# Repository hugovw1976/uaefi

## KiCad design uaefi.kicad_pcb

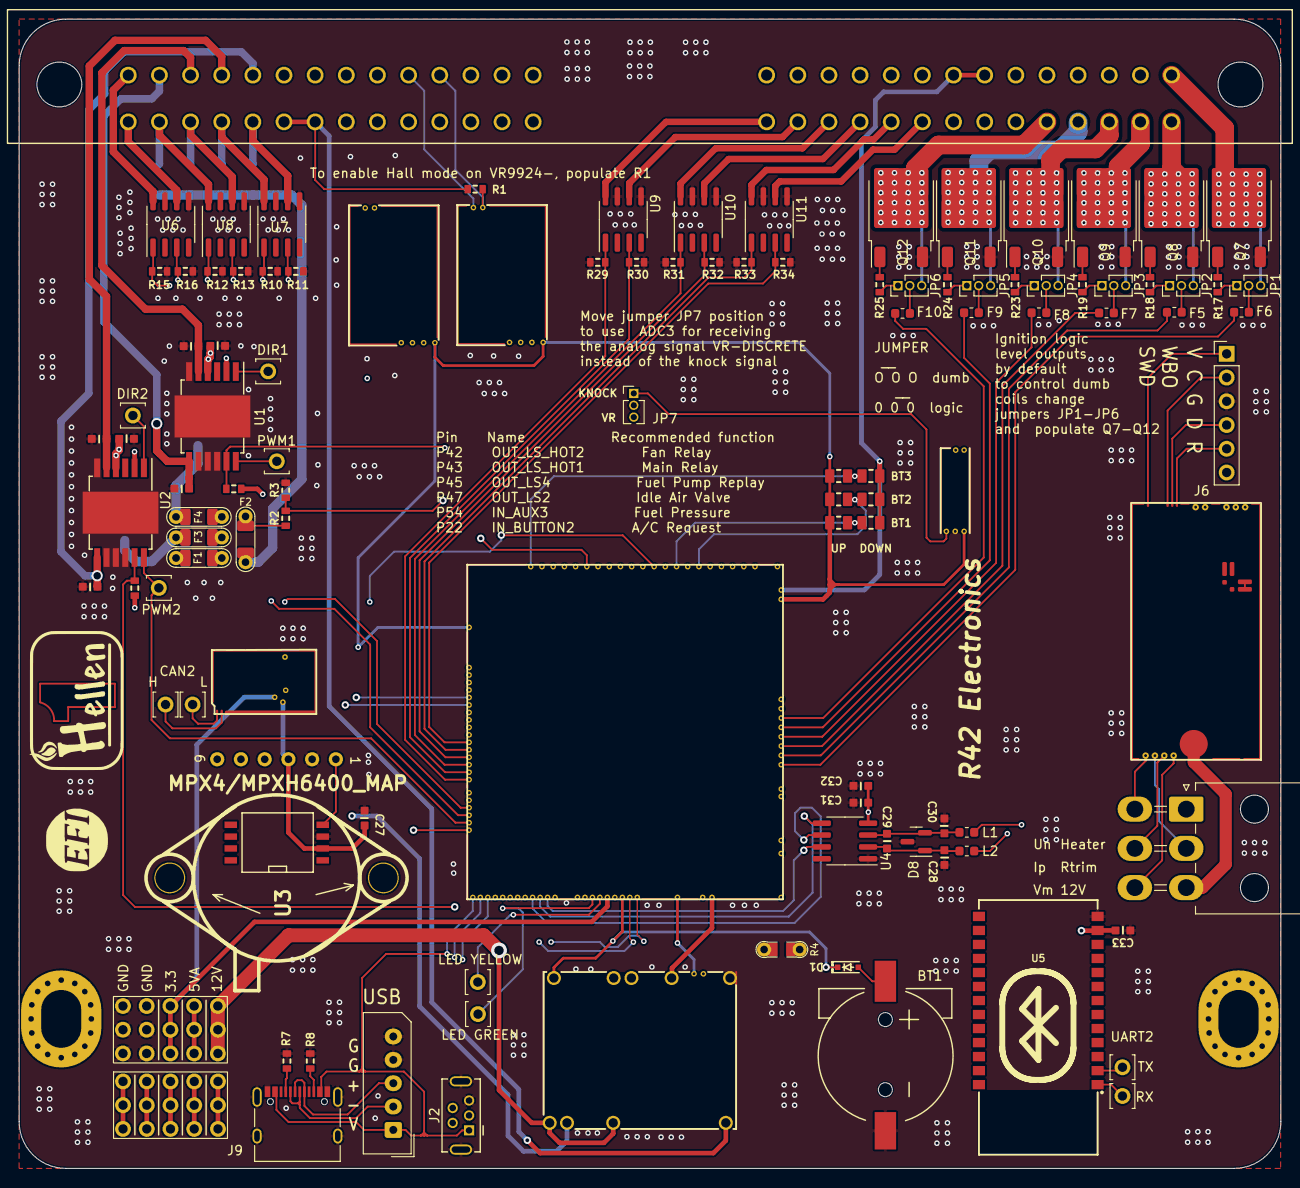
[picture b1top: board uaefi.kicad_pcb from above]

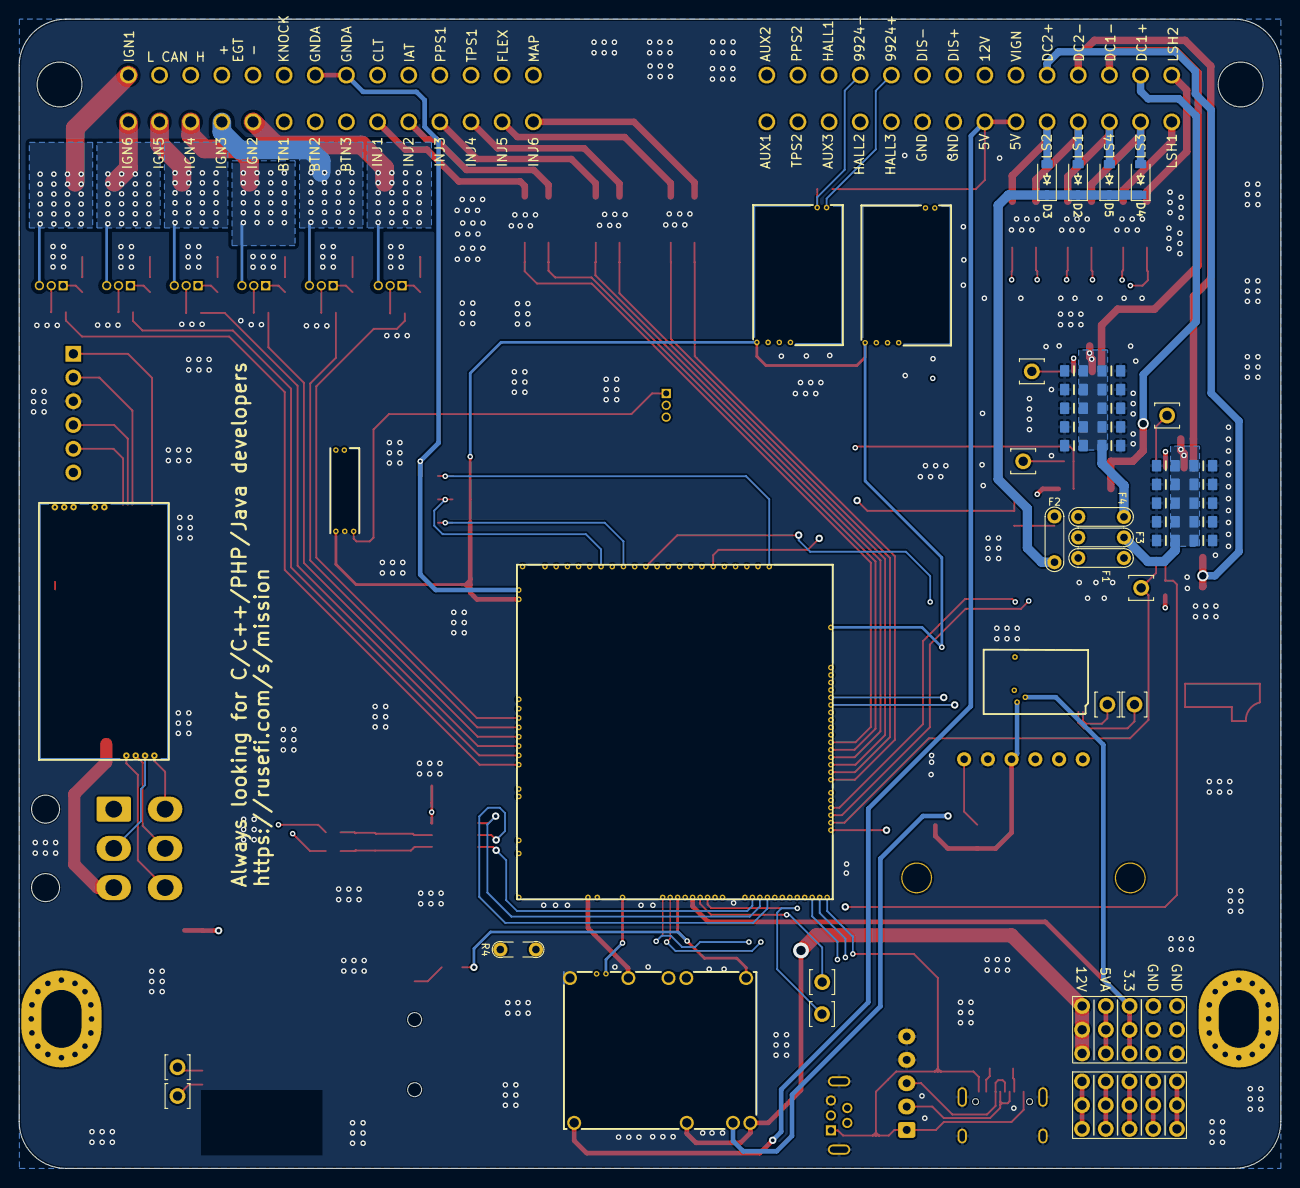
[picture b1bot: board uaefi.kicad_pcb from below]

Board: 4 copper layers, 135.0 x 123.0 mm, 137 parts (24 on the bottom side), 151 nets.

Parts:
BT1: CR1220; CR1220-2
C1, C2, C3, C4, C5, C6, C7, C8, C9, C10, C14, C15, C16, C17, C18, C19, C20, C21, C22, C23: 10u; C0805
C11, C24, C27, C29, C31, C33: 100n; C0603
C12, C13, C25, C26, C28, C30: 10n; C0603
C32: 1u; C0603
D1: 1N4148WS; SOD-323
D2, D3, D4, D5: B5819W; SOD-123
D8: NUP2105L; SOT-23
F1, F2, F3, F4: 12H1500D; PAD-1206-PAD
F5, F6, F7, F8, F9, F10: 50mA; Fuse_0603_1608Metric
G1: RUSEFI_LOGO; rusefi_logo
G2: LOGO
G3, G4: PROTO_AREA
H1: M4; MountingHole_4.3x6.2mm_M4_Pad_Via
H2: M3; MountingHole_4.3x6.2mm_M4_Pad_Via
J1: 211PL562L0011; 211PL562L0011_2
J2: USB_B_Mini; USB-MINI-B-VERTICAL
J3: 5569-06A2; Molex_Mini-Fit_Jr_5569-06A2_2x03_P4.20mm_Horizontal
J6: Conn_01x06; PinHeader_1x06_P2.54mm_Vertical
J7: Conn_01x05_Male; Molex_SPOX_5267-05A_1x05_P2.50mm_Vertical
J9: USB_C
JP1, JP2, JP3, JP4, JP5, JP6, JP7: Jumper_3_Open; PinHeader_1x03_P1.27mm_Vertical
L1, L2: 470R@100MHz; L_0603_1608Metric
M1: Module-power_12and5V-0.2; power_12and5V
M2: Module-knock-0.2; knock
M3: Module-vr-discrete-0.5; vr-discrete
M4: Module-vr-max9924-0.1; vr-max9924
M5: Module-wbo-0.5; wbo
M6: Module:mega-mcu100/0.3; mega-mcu100
M7: Module-can-0.1; can
P1, P2, P3, P4, P7, P8, P15, P16, P17, P18: Pad; PAD-TH
Q7, Q8, Q9, Q10, Q11, Q12: ISL9V3040D3ST; TO-252-2
R1, R9, R10, R11, R12, R13, R14, R15, R16, R29, R30, R31, R32, R33, R34: 4.7k; R0603
R2: 33k; R0603
R3: 6.8k; R0603
R4: Jumper-Pad-Pad; PAD-0805-PAD
R7, R8: 5.6k; R0603
R17, R18, R19, R23, R24, R25: 22; R0603
R35, R36, R37: 10k; R0805
R38, R39, R40: DNP; R0805
U1, U2: TLE9201SG; Infineon_PG-DSO-12-11
U3: MPX4/MPXH6400_MAP; MPX-4_MAP
U4: MAX31855KASA; SOIC-8_3.9x4.9mm_P1.27mm
U5: JDY-33
U6, U7, U8, U9, U10, U11: VNLD5160TR-E; SOIC-8_3.9x4.9mm_P1.27mm

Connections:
+3.3V: M6.N21 (V33), R9.2, R14.2, U1.2 (VSO), U2.2 (VSO)
+3.3VA: C31.2, C32.2, C33.2, G3.3, G3.8, G3.13, M6.N15 (V33_SWITCHABLE), M7.V2 (CAN_VIO), U4.4 (V_CC), U5.12 (3V3)
+5V: M1.E4 (V5), M6.N22 (VCC)
+5VA: C27.2, G3.4, G3.9, G3.14, M2.E1 (V5A), M3.E4 (V5_IN), M4.E4 (V5_IN), M5.W1 (V5_IN), M6.E1 (V5A_SWITCHABLE), M6.W2 (V5A_SWITCHABLE), M7.V1 (V5), R38.2, R39.2, R40.2, U3.3 (VCC)
+5VP: J1.P48 (48), J1.P49 (49), M1.V4 (5VP), R1.1
+12V: F2.1, F3.1, F4.1, J1.P37 (37), R2.2
+12V_RAW: D2.1 (K), D3.1 (K), D4.1 (K), D5.1 (K), F2.2, G3.5, G3.10, G3.15, J3.1, M1.V1 (V12_PERM), M1.V3 (V12_RAW)
/12V_KEY: F1.1, J1.P36 (36)
/ADC3: JP7.2 (C), M6.S15 (IN_KNOCK_(PA2))
/CAN+: J1.P3 (3), M5.W4 (CANH), M6.W11 (CANH)
/CAN-: J1.P2 (2), M5.W3 (CANL), M6.W12 (CANL)
/DC1_DIR: M6.E21 (OUT_PWM4_(PC8)), P15.1, U1.1 (DIR)
/DC1_DIS: M6.E8 (SPI2_MISO_(PB14)), R9.1, U1.11 (DIS)
/DC1_PWM: M6.E20 (OUT_PWM3_(PC7)), P17.1, U1.12 (PWM)
/DC2_DIR: M6.E9 (SPI2_MOSI_(PB15)), P16.1, U2.1 (DIR)
/DC2_DIS: M6.N4 (USBID_(PA10)), R14.1, U2.11 (DIS)
/DC2_PWM: M6.E22 (OUT_PWM5_(PC9)), P18.1, U2.12 (PWM)
/DC Driver 1/PWR: C1.2, C2.2, C3.2, C4.2, C5.2, C6.2, C7.2, C8.2, C9.2, C10.2, C11.2, F4.2, U1.4 (VS)
/DC Driver 2/PWR: C14.2, C15.2, C16.2, C17.2, C18.2, C19.2, C20.2, C21.2, C22.2, C23.2, C24.2, F3.2, U2.4 (VS)
/EGT+: J1.P4 (4), L1.1
/EGT-: J1.P5 (5), L2.1
/EGT/SPI_CS: M6.N9 (SPI3_CS_(PA15)), U4.6 (~CS)
/EGT/SPI_SCK: M6.N10 (SPI3_SCK_(PC10)), U4.5 (SCK)
/EGT/SPI_SO: M6.N11 (SPI3_MISO_(PC11)), U4.7 (SO)
/IGN1: F6.2, M6.W10 (IGN1_(PC13))
/IGN2: F5.2, M6.W9 (IGN2_(PE5))
/IGN3: F7.2, M6.W8 (IGN3_(PE4))
/IGN4: F8.2, M6.W7 (IGN4_(PE3))
/IGN5: F9.2, M6.W6 (IGN5_(PE2))
/IGN6: F10.2, M6.W5 (IGN6_(PB8))
/INJ1: M6.E17 (OUT_INJ1_(PD3)), R29.2, U9.1 (IN1)
/INJ2: M6.E16 (OUT_INJ2_(PA9)), R30.2, U9.3 (IN2)
/INJ3: M6.E15 (OUT_INJ3_(PD11)), R31.2, U10.1 (IN1)
/INJ4: M6.E14 (OUT_INJ4_(PD10)), R32.2, U10.3 (IN2)
/INJ5: M6.E13 (OUT_INJ5_(PD2)), R33.2, U11.1 (IN1)
/INJ6: M6.E12 (OUT_INJ6_(PA8)), R34.2, U11.3 (IN2)
/INTERNAL_MAP: M6.S12 (IN_MAP2_(PC1)), U3.1 (VOUT)
/IN_AUX1: J1.P56 (56), M6.S11 (IN_O2S_/_CAN_WAKEUP_(PA0))
/IN_AUX2: J1.P29 (29), M6.S10 (IN_O2S2_(PA1))
/IN_AUX3: J1.P54 (54), M6.S7 (IN_AUX3_(PA7))
/IN_BUTTON1: J1.P23 (23), M6.S14 (IN_CRANK_(PB1)), R35.2, R38.1
/IN_BUTTON2: J1.P22 (22), M6.S16 (IN_CAM_(PA6)), R36.2, R39.1
/IN_BUTTON3: J1.P21 (21), M6.S1 (IN_D4_(PE15)), R37.2, R40.1
/IN_CLT: J1.P9 (9), M6.S21 (IN_CLT_(PC2))
/IN_FLEX: J1.P13 (13), M6.S17 (IN_VSS_(PE11))
/IN_HALL1: J1.P31 (31), M6.S4 (IN_D1_(PE12))
/IN_HALL2: J1.P53 (53), M6.S3 (IN_D2_(PE13))
/IN_HALL3: J1.P52 (52), M6.S2 (IN_D3_(PE14))
/IN_IAT: J1.P10 (10), M6.S20 (IN_IAT_(PC3))
/IN_KNOCK: JP7.1 (A), M2.E3 (OUT_KNOCK)
/IN_KNOCK_RAW: J1.P6 (6), M2.W1 (IN_KNOCK)
/IN_MAP: J1.P14 (14), M6.S13 (IN_MAP1_(PC0))
/IN_PPS1: J1.P11 (11), M6.S19 (IN_PPS_(PA3))
/IN_PPS2: J1.P30 (30), M6.S8 (IN_AUX2_(PC4/PE9))
/IN_TPS1: J1.P12 (12), M6.S18 (IN_TPS_(PA4))
/IN_TPS2: J1.P55 (55), M6.S9 (IN_AUX1_(PB0))
/IN_VIGN: F1.2, M1.V2 (IN_VIGN)
/IN_VMAIN: M6.S6 (IN_AUX4_(PC5)), R2.1, R3.2
/LS1: M6.E11 (OUT_INJ7_(PD15)), R10.2, U7.1 (IN1)
/LS2: M6.E10 (OUT_INJ8_(PD12)), R11.2, U7.3 (IN2)
/LS3: M6.E18 (OUT_PWM1_(PD13)), R12.2, U8.1 (IN1)
/LS4: M6.E19 (OUT_PWM2_(PC6)), R13.2, U8.3 (IN2)
/LS_HOT1: M6.W4 (IGN7_(PB9)), R16.1, U6.3 (IN2)
/LS_HOT2: M6.W3 (IGN8_(PE6)), R15.1, U6.1 (IN1)
/OUT_DC1+: C13.2, J1.P41 (41), U1.7 (OUT2)
/OUT_DC1-: C12.2, J1.P40 (40), U1.5 (OUT1)
/OUT_DC2+: C26.2, J1.P38 (38), U2.7 (OUT2)
/OUT_DC2-: C25.2, J1.P39 (39), U2.5 (OUT1)
/OUT_IGN1: J1.P1 (1), JP1.3 (B), Q7.2 (C)
/OUT_IGN2: J1.P28 (28), JP2.3 (B), Q8.2 (C)
/OUT_IGN3: J1.P27 (27), JP3.3 (B), Q9.2 (C)
/OUT_IGN4: J1.P26 (26), JP4.3 (B), Q10.2 (C)
/OUT_IGN5: J1.P25 (25), JP5.3 (B), Q11.2 (C)
/OUT_IGN6: J1.P24 (24), JP6.3 (B), Q12.2 (C)
/OUT_INJ1: J1.P15 (15), U9.8 (D1)
/OUT_INJ2: J1.P16 (16), U9.6 (D2)
/OUT_INJ3: J1.P17 (17), U10.8 (D1)
/OUT_INJ4: J1.P18 (18), U10.6 (D2)
/OUT_INJ5: J1.P19 (19), U11.8 (D1)
/OUT_INJ6: J1.P20 (20), U11.6 (D2)
/OUT_LS1: D2.2 (A), J1.P46 (46), U7.8 (D1)
/OUT_LS2: D3.2 (A), J1.P47 (47), U7.6 (D2)
/OUT_LS3: D4.2 (A), J1.P44 (44), U8.8 (D1)
/OUT_LS4: D5.2 (A), J1.P45 (45), U8.6 (D2)
/OUT_LS_HOT1: J1.P43 (43), U6.6 (D2)
/OUT_LS_HOT2: J1.P42 (42), U6.8 (D1)
/PG_5VP: M6.N12 (SPI3_MOSI_(PC12)), R4.2
/PWR_EN: M1.E5 (EN_5VP), M6.N20 (OUT_PWR_EN_(PE10))
/USB+: J2.3 (D+), J7.3, J9.A6 (D+), J9.B6 (D+), M6.N3 (USBP_(PA12))
/USB-: J2.2 (D-), J7.2, J9.A7 (D-), J9.B7 (D-), M6.N2 (USBM_(PA11))
/VBAT: D1.1 (K), M1.E1 (VBAT), M6.N17 (VBAT)
/VBUS: J2.1 (VBUS), J7.1, J9.A4 (VBUS), J9.A9 (VBUS), J9.B4 (VBUS), J9.B9 (VBUS), M6.N1 (VBUS)
/VIGN: M1.E3 (VIGN), M6.E5 (IN_VIGN_(PA5))
/VREF1: M2.W2 (VREF), M6.S22 (VREF1)
/VR_DISCRETE: M3.E3 (OUT), M6.N18 (UART8_RX_(PE0))
/VR_DISCRETE+: J1.P35 (35), M3.W2 (VR+)
/VR_DISCRETE-: J1.P34 (34), M3.W1 (VR-)
/VR_DISCRETE_A: JP7.3 (B), M3.E2 (OUT_A)
/VR_DISCRETE_THR: M3.E1 (Thresh_IN), M6.E23 (OUT_PWM6_(PD14))
/VR_MAX9924: M4.E3 (OUT), M6.N19 (UART8_TX_(PE1))
/VR_MAX9924+: J1.P33 (33), M4.W2 (VR+)
/VR_MAX9924-: J1.P32 (32), M4.W1 (VR-), R1.2
/WBO_Heater: J3.3, M5.E5 (LSU_H+)
/WBO_Ip: J3.5, M5.E3 (LSU_Ip)
/WBO_Rtrim: J3.2, M5.E4 (LSU_Rtrim)
/WBO_Un: J3.4, M5.E1 (LSU_Un)
/WBO_Vm: J3.6, M5.E2 (LSU_Vm)
GND: BT1.2 (-), C1.1, C2.1, C3.1, C4.1, C5.1, C6.1, C7.1, C8.1, C9.1, C10.1, C11.1, C12.1, C13.1, C14.1, C15.1, C16.1, C17.1, C18.1, C19.1, C20.1, C21.1, C22.1, C23.1, C24.1, C25.1, C26.1, C27.1, C28.1, C30.1, C31.1, C32.1, C33.1, D8.3 (A), G3.1, G3.2, G3.6, G3.7, G3.11, G3.12, J1.P50 (50), J1.P51 (51), J2.5 (GND), J2.6 (Shield), J6.3, J7.4, J7.5, J9.A1 (GND), J9.A12 (GND), J9.B1 (GND), J9.B12 (GND), J9.S1 (SHIELD), M1.S1 (GND), M2.E2 (GND), M3.G (GND), M4.G (GND), M5.E6 (LSU_H-), M5.G (GND), M6.G (GND), M7.E1 (GND), Q7.3 (E), Q8.3 (E), Q9.3 (E), Q10.3 (E), Q11.3 (E), Q12.3 (E), R3.1, R7.1, R8.1, R10.1, R11.1, R12.1, R13.1, R15.2, R16.2, R29.1, R30.1, R31.1, R32.1, R33.1, R34.1, U1.6 (GND), U1.8 (SI), U1.9 (CSN), U1.10 (SCK), U1.13 (GND), U2.6 (GND), U2.8 (SI), U2.9 (CSN), U2.10 (SCK), U2.13 (GND), U3.2 (GND), U4.1 (GND), U5.13 (GND), U6.5 (S2), U6.7 (S1), U7.5 (S2), U7.7 (S1), U8.5 (S2), U8.7 (S1), U9.5 (S2), U9.7 (S1), U10.5 (S2), U10.7 (S1), U11.5 (S2), U11.7 (S1)
GNDA: J1.P7 (7), J1.P8 (8), M6.W1 (GNDA), R35.1, R36.1, R37.1
unnamed: BT1.1 (+), D1.2 (A)
unnamed: G4.1, G4.6, G4.11
unnamed: G4.5, G4.10, G4.15
unnamed: G4.2, G4.7, G4.12
unnamed: G4.3, G4.8, G4.13
unnamed: G4.4, G4.9, G4.14
unnamed: J6.1, M5.W8 (V33_OUT)
unnamed: J6.2, M5.W7 (SWCLK)
unnamed: J6.4, M5.W6 (SWDIO)
unnamed: J6.5, M5.W5 (nReset)
unnamed: J9.A5 (CC1), R7.2
unnamed: J9.B5 (CC2), R8.2
unnamed: JP1.1 (A), R17.2
unnamed: F6.1, JP1.2 (C)
unnamed: JP2.1 (A), R18.2
unnamed: F5.1, JP2.2 (C)
unnamed: JP3.1 (A), R19.2
unnamed: F7.1, JP3.2 (C)
unnamed: JP4.1 (A), R23.2
unnamed: F8.1, JP4.2 (C)
unnamed: JP5.1 (A), R24.2
unnamed: F9.1, JP5.2 (C)
unnamed: JP6.1 (A), R25.2
unnamed: F10.1, JP6.2 (C)
unnamed: M1.E6 (PG_5VP), R4.1
unnamed: M5.J1 (SEL1), M5.J_GND1 (PULL_DOWN1)
unnamed: M6.N14a (LED_GREEN), P4.1
unnamed: M6.N14b (LED_YELLOW), P3.1
unnamed: M6.E6 (SPI2_CS_/_CAN2_RX_(PB12)), M7.V6 (CAN_RX)
unnamed: M6.E7 (SPI2_SCK_/_CAN2_TX_(PB13)), M7.V5 (CAN_TX)
unnamed: M6.N14 (UART2_RX_(PD6)), P7.1, U5.1 (TXD)
unnamed: M6.N13 (UART2_TX_(PD5)), P8.1, U5.2 (RXD)
unnamed: M7.S2 (CANH), P2.1
unnamed: M7.S1 (CANL), P1.1
unnamed: Q7.1 (G), R17.1
unnamed: Q8.1 (G), R18.1
unnamed: Q9.1 (G), R19.1
unnamed: Q10.1 (G), R23.1
unnamed: Q11.1 (G), R24.1
unnamed: Q12.1 (G), R25.1
unnamed: C29.2, C30.2, D8.2 (K), L1.2, U4.3 (T+)
unnamed: C28.2, C29.1, D8.1 (K), L2.2, U4.2 (T-)

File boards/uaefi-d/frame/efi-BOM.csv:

Comment,Designator,Footprint,LCSC Part #
"CR1220","BT1","CR1220-2","C70381"
"10u","C1","C0805","C15850"
"10u","C2","C0805","C15850"
"10u","C3","C0805","C15850"
"10u","C4","C0805","C15850"
"10u","C5","C0805","C15850"
"10u","C6","C0805","C15850"
"10u","C7","C0805","C15850"
"10u","C8","C0805","C15850"
"10u","C9","C0805","C15850"
"10u","C10","C0805","C15850"
"100n","C11","C0603","C14663"
"10n","C12","C0603","C57112"
"10n","C13","C0603","C57112"
"10u","C14","C0805","C15850"
"10u","C15","C0805","C15850"
"10u","C16","C0805","C15850"
"10u","C17","C0805","C15850"
"10u","C18","C0805","C15850"
"10u","C19","C0805","C15850"
"10u","C20","C0805","C15850"
"10u","C21","C0805","C15850"
"10u","C22","C0805","C15850"
"10u","C23","C0805","C15850"
"100n","C24","C0603","C14663"
"10n","C25","C0603","C57112"
"10n","C26","C0603","C57112"
"100n","C27","C0603","C14663"
"10n","C28","C0603","C57112"
"100n","C29","C0603","C14663"
"10n","C30","C0603","C57112"
"100n","C31","C0603","C14663"
"1u","C32","C0603","C15849"
"100n","C33","C0603","C14663"
"1N4148WS","D1","SOD-323","C2128"
"B5819W","D2","SOD-123","C8598"
"B5819W","D3","SOD-123","C8598"
"B5819W","D4","SOD-123","C8598"
"B5819W","D5","SOD-123","C8598"
"NUP2105L","D8","SOT-23","C284104"
"12H1500D","F1","PAD-1206-PAD","C182446"
"12H1500D","F2","PAD-1206-PAD","C182446"
"12H1500D","F3","PAD-1206-PAD","C182446"
"12H1500D","F4","PAD-1206-PAD","C182446"
"50mA","F5","Fuse_0603_1608Metric","C369141"
"50mA","F6","Fuse_0603_1608Metric","C369141"
"50mA","F7","Fuse_0603_1608Metric","C369141"
"50mA","F8","Fuse_0603_1608Metric","C369141"
"50mA","F9","Fuse_0603_1608Metric","C369141"
"50mA","F10","Fuse_0603_1608Metric","C369141"
"RUSEFI_LOGO","G1","rusefi_logo",""
"LOGO","G2","LOGO",""
"PROTO_AREA","G3","PROTO_AREA",""
"PROTO_AREA","G4","PROTO_AREA",""
"M4","H1","MountingHole_4.3x6.2mm_M4_Pad_Via",""
"M3","H2","MountingHole_4.3x6.2mm_M4_Pad_Via",""
"211PL562L0011","J1","211PL562L0011_2",""
"USB_B_Mini","J2","USB-MINI-B-VERTICAL",""
"5569-06A2","J3","Molex_Mini-Fit_Jr_5569-06A2_2x03_P4.20mm_Horizontal","C293509"
"Conn_01x06","J6","PinHeader_1x06_P2.54mm_Vertical","C37208"
"Conn_01x05_Male","J7","Molex_SPOX_5267-05A_1x05_P2.50mm_Vertical",""
"USB_C","J9","USB_C","C2927038"
"Jumper_3_Open","JP1","PinHeader_1x03_P1.27mm_Vertical","C124354"
"Jumper_3_Open","JP2","PinHeader_1x03_P1.27mm_Vertical","C124354"
"Jumper_3_Open","JP3","PinHeader_1x03_P1.27mm_Vertical","C124354"
"Jumper_3_Open","JP4","PinHeader_1x03_P1.27mm_Vertical","C124354"
"Jumper_3_Open","JP5","PinHeader_1x03_P1.27mm_Vertical","C124354"
"Jumper_3_Open","JP6","PinHeader_1x03_P1.27mm_Vertical","C124354"
"Jumper_3_Open","JP7","PinHeader_1x03_P1.27mm_Vertical",""
"470R@100MHz","L1","L_0603_1608Metric","C97853"
"470R@100MHz","L2","L_0603_1608Metric","C97853"
"Module:power_12and5V/0.2","M1","power_12and5V",""
"Module:knock/0.2","M2","knock",""
"Module:vr-discrete/0.5","M3","vr-discrete",""
"Module:vr-max9924/0.1","M4","vr-max9924",""
"Module:wbo/0.5","M5","wbo",""
"Module:mega-mcu100/0.3","M6","mega-mcu100",""
"Module:can/0.1","M7","can",""
"Pad","P1","PAD-TH",""
"Pad","P2","PAD-TH",""
"Pad","P3","PAD-TH",""
"Pad","P4","PAD-TH",""
"Pad","P7","PAD-TH",""
"Pad","P8","PAD-TH",""
"Pad","P15","PAD-TH",""
"Pad","P16","PAD-TH",""
"Pad","P17","PAD-TH",""
"Pad","P18","PAD-TH",""
"ISL9V3040D3ST","Q7","DPAK","C603080"
"ISL9V3040D3ST","Q8","DPAK","C603080"
"ISL9V3040D3ST","Q9","DPAK","C603080"
"ISL9V3040D3ST","Q10","DPAK","C603080"
"ISL9V3040D3ST","Q11","DPAK","C603080"
"ISL9V3040D3ST","Q12","DPAK","C603080"
"4.7k","R1","R0603",""
"33k","R2","R0603","C4216"
"6.8k","R3","R0603","C23212"
"Jumper-Pad-Pad","R4","PAD-0805-PAD","C17477"
"5.6k","R7","R0603","C23189"
"5.6k","R8","R0603","C23189"
"4.7k","R9","R0603","C23162"
"4.7k","R10","R0603","C23162"
"4.7k","R11","R0603","C23162"
"4.7k","R12","R0603","C23162"
"4.7k","R13","R0603","C23162"
"4.7k","R14","R0603","C23162"
"4.7k","R15","R0603","C23162"
"4.7k","R16","R0603","C23162"
"22","R17","R0603","C23345"
"22","R18","R0603","C23345"
"22","R19","R0603","C23345"
"22","R23","R0603","C23345"
"22","R24","R0603","C23345"
"22","R25","R0603","C23345"
"4.7k","R29","R0603","C23162"
"4.7k","R30","R0603","C23162"
"4.7k","R31","R0603","C23162"
"4.7k","R32","R0603","C23162"
"4.7k","R33","R0603","C23162"
"4.7k","R34","R0603","C23162"
"10k","R35","R0805","C17414"
"10k","R36","R0805","C17414"
"10k","R37","R0805","C17414"
"DNP","R38","R0805",""
"DNP","R39","R0805",""
"DNP","R40","R0805",""
"TLE9201SG","U1","Infineon_PG-DSO-12-11","C112633"
"TLE9201SG","U2","Infineon_PG-DSO-12-11","C112633"
"MPX4/MPXH6400_MAP","U3","MPX-4_MAP",""
"MAX31855KASA","U4","SO8","C52028"
"JDY-33","U5","JDY-33","C9900001612"
"VNLD5160TR-E","U6","SO8","C377942"
"VNLD5160TR-E","U7","SO8","C377942"
"VNLD5160TR-E","U8","SO8","C377942"
"VNLD5160TR-E","U9","SO8","C377942"
"VNLD5160TR-E","U10","SO8","C377942"
"VNLD5160TR-E","U11","SO8","C377942"

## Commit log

2024-05-16 Rev.D
2024-05-16 [skip actions] Auto-generated board v2.1
2024-05-16 Reev.D update
2024-05-18 Rev.D update
2024-05-24 Add Heatsink
